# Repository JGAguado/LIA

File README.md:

[![License: CC BY-NC-SA 4.0][license-shield]](LICENSE)
[![Project Maintenance][maintenance-shield]][maintenance]
[![Powered by Meshtastic][meshtastic-shield]][meshtastic]
[![Documentation][docs-shield]][docs]

<p align="center">
    <picture>
      <source media="(prefers-color-scheme: dark)" srcset="https://raw.githubusercontent.com/JGAguado/LIA/main/website/src/assets/brand/Primary%20dark.png">
      <source media="(prefers-color-scheme: light)" srcset="https://raw.githubusercontent.com/JGAguado/LIA/main/website/src/assets/brand/Primary%20light.png">
      
    </picture>
</p>

**LIA** is an open-source, low-power pet and asset tracker built on top of [Meshtastic](https://meshtastic.org/) and LoRa mesh networking. It's designed to be a compact, long-range, subscription-free tracking device that keeps working off-grid — no cell coverage, no monthly fee, no cloud dependency.

📖 **[Read the full documentation](https://jgaguado.github.io/LIA/)**

<p align="center">
    
</p>

---

## Features

- Long-range LoRa communication over the open Meshtastic protocol
- GPS/GNSS location tracking, sent only as a direct message to a predefined target node — not visible to the wider public mesh
- A physical 3-position mode switch: continuous tracking (LED on, position every 30s), a low-power sleep cycle (wake roughly once a minute, get a fix, report it, sleep again), or fully OFF (cuts power to the MCU while still allowing the battery to charge)
- A text-command interface over the mesh: query position/battery on demand, toggle charge/motion notifications, override the status LED — see [Meshtastic Configuration](https://jgaguado.github.io/LIA/docs/firmware/meshtastic-configuration/)
- Deep-sleep, low-power firmware with real hardware wake sources (timer, mode-switch flip, charger plug-in)
- Subscription-free — no cloud backend required
- Fully open hardware: schematics, PCB layout, BOM, and enclosure CAD
- Compact, collar-mountable, waterproof-by-design enclosure — in three variants, see below

## Hardware Stack

**Core components**

- ESP32-S3-MINI-1 (MCU, Wi-Fi/BLE)
- SX1262 LoRa transceiver
- u-blox SAM-M10Q GNSS module
- MAX17048 battery fuel gauge

**Two hardware revisions, one firmware**

Both revisions carry the same reworked LSM6DSOXTR 6-axis IMU and run the identical `lia_v1` firmware — the only difference is the battery/enclosure:

- **V1.0** — 18650 Li-ion cell (3500 mAh) with magnetic pogo charging.
- **V1.1** — a 50×37×4 mm pouch cell (1000 mAh) instead, trading capacity for a much more compact enclosure.

**Antennas**

- Internal FPC LoRa antenna, or alternatively a standard omnidirectional linear 868/915 MHz antenna (e.g. [Seeed's LoRa Antenna Kit](https://www.seeedstudio.com/LoRa-Antenna-Kit-for-reTerminal-DM-p-5714.html))
- Ceramic GNSS patch antenna

See [Hardware documentation](https://jgaguado.github.io/LIA/docs/hardware/pcb/) for full details, and [Enclosure](https://jgaguado.github.io/LIA/docs/hardware/enclosure/) for the enclosure variants that pair with these boards.

## Software Stack

- [Meshtastic](https://meshtastic.org/) firmware
- [Astro](https://astro.build/) + [Starlight](https://starlight.astro.build/) + [Tailwind CSS](https://tailwindcss.com/) for this documentation site (fully static, no backend, no analytics, no cookies)

## Repository Structure

```
LIA/
├── website/       Astro + Starlight documentation & marketing site
├── firmware/       Meshtastic-based firmware (board variants, services, drivers, build tooling)
├── hardware/       KiCad project, PCB renders, schematics, BOM, production files
├── enclosure/       Enclosure CAD (gitignored native files), STEP/STL exports, renders — V1.0-Detachable/, V1.0-Fixed/, V1.1-Fixed/
├── mobile/         Companion mobile app (planned)
├── scripts/       Repo maintenance and tooling scripts
├── .github/       CI/CD workflows, issue & PR templates
├── LICENSE
├── CONTRIBUTING.md
├── CODE_OF_CONDUCT.md
└── README.md
```

## Quick Start

**Browse the docs:** https://jgaguado.github.io/LIA/

**Run the website locally:**

```sh
cd website
npm install
npm run dev
```

**Hardware:** open [`hardware/kicad/LIA.kicad_pro`](hardware/kicad/LIA.kicad_pro) in [KiCad](https://www.kicad.org/) 8+.

**Enclosure:** three versions — [`enclosure/V1.0-Detachable/`](enclosure/V1.0-Detachable), [`enclosure/V1.0-Fixed/`](enclosure/V1.0-Fixed), [`enclosure/V1.1-Fixed/`](enclosure/V1.1-Fixed) — each with its own `step/`/`stl/` exports and `drawings/`; no CAD license required to view or print them. See [Enclosure docs](https://jgaguado.github.io/LIA/docs/hardware/enclosure/) for what differs between them.

**Firmware:** see [`firmware/README.md`](firmware/README.md) and the [Getting Started guide](https://jgaguado.github.io/LIA/docs/getting-started/).

## Contributing

Contributions are welcome across hardware, firmware, mechanical design, and documentation. See [CONTRIBUTING.md](CONTRIBUTING.md) for how to get set up, and [CODE_OF_CONDUCT.md](CODE_OF_CONDUCT.md) for community guidelines.

## License

LIA is released under **[CC BY-NC-SA 4.0](LICENSE)** (Attribution-NonCommercial-ShareAlike). Personal, educational, and community use is welcome; commercial use requires permission from the maintainers. See the [License page](https://jgaguado.github.io/LIA/docs/license/) for details.

## Roadmap
- [x] Draft project requirements and design goals
- [x] Complete first hardware revision (V1.0) and a second, more compact revision (V1.1)
- [x] Complete first enclosure revisions — V1.0-Detachable, V1.0-Fixed, and V1.1-Fixed
- [x] Manufacture and assemble first batch of boards
- [x] Smoke-test and validate hardware (radio, GPS, charging, battery gauge, IMU)
- [x] Release first firmware — see [Development History](https://jgaguado.github.io/LIA/docs/development-history/) for the phase-by-phase log
- [x] Release initial documentation
- [x] Field trial: real-world tracking validation over an extended period
- [x] Measured (not estimated) battery runtime numbers

## Disclaimer

LIA is an experimental open-source project and should not be considered a guaranteed real-time safety tracking solution.

[license-shield]: https://img.shields.io/badge/License-CC%20BY--NC--SA%204.0-lightgrey.svg?style=for-the-badge
[maintenance-shield]: https://img.shields.io/badge/maintainer-J.%20G.%20Aguado-2e48a7.svg?style=for-the-badge
[maintenance]: https://github.com/JGAguado
[meshtastic-shield]: https://img.shields.io/badge/Powered%20by-Meshtastic-67EA94.svg?style=for-the-badge
[meshtastic]: https://meshtastic.org/
[docs-shield]: https://img.shields.io/badge/Documentation-online-2e48a7.svg?style=for-the-badge
[docs]: https://jgaguado.github.io/LIA/

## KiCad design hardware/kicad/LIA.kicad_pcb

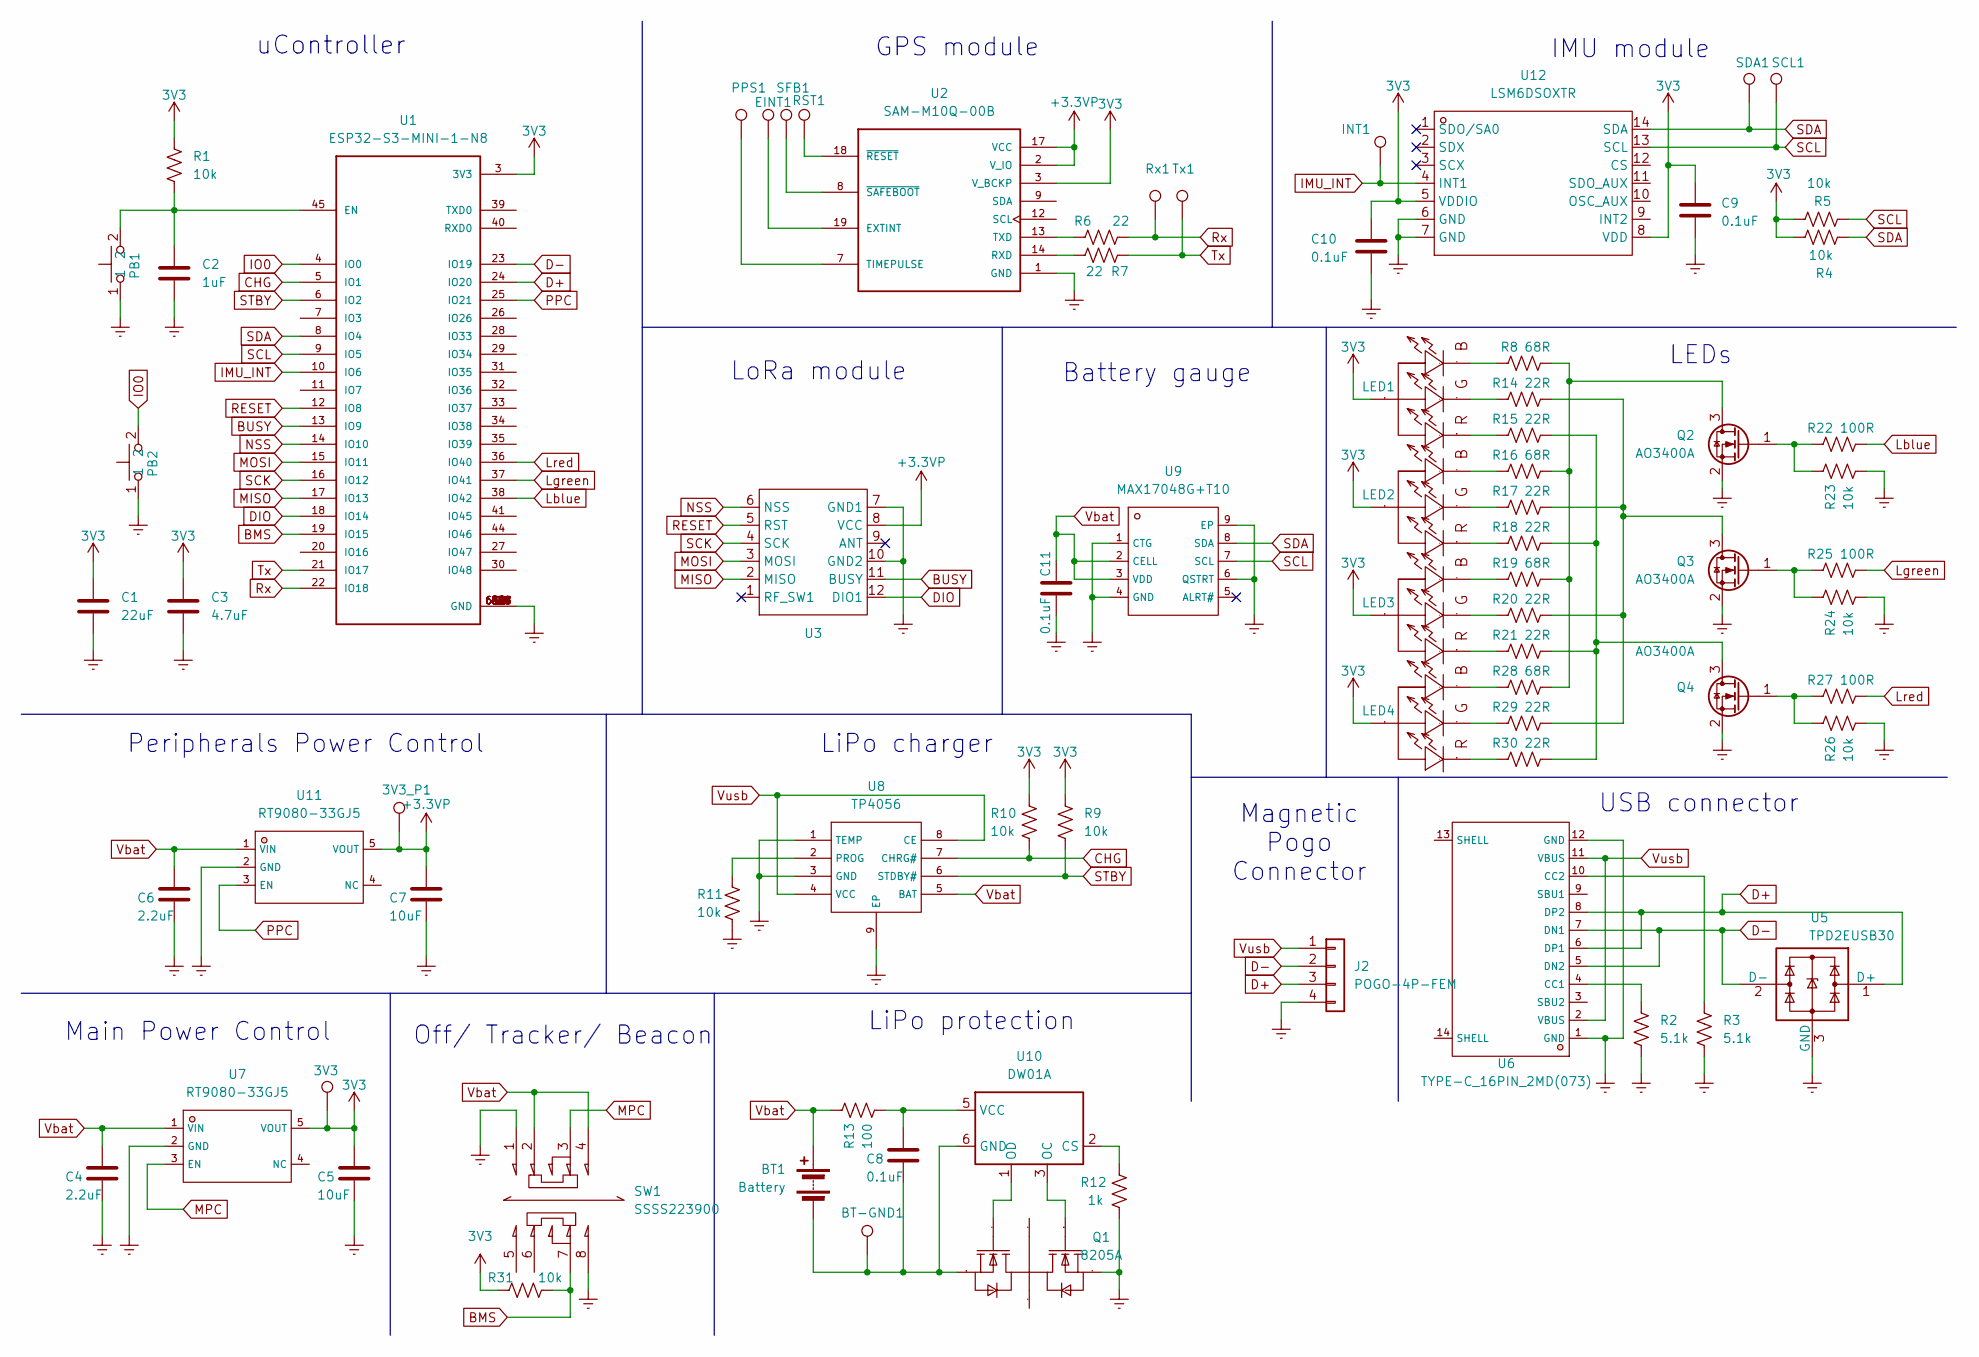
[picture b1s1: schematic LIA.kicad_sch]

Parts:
3V3, 3V3_P1: TestPoint; TestPoint_Pad_D1.0mm
BT1: Battery; BatteryClip_Keystone_54_D16-19mm
BT-GND1: TestPoint; TestPoint_Pad_D1.0mm
C1: 22uF; C_0805_2012Metric
C2: 1uF; C_0201_0603Metric
C3: 4.7uF; C_0201_0603Metric
C4, C6: 2.2uF; C_0201_0603Metric
C5, C7: 10uF; C_0603_1608Metric
C8, C9, C10, C11: 0.1uF; C_0201_0603Metric
EINT1: TestPoint; TestPoint_Pad_D1.0mm
INT1: TestPoint; TestPoint_Pad_D1.0mm
J2: POGO-4P-FEM; POGO-MAG-4P-FEM
LED1, LED2, LED3, LED4: MHS110CRGBCT; LED-SMD_4P-L3.2-W1.1_TJ-S3210SW5TCGLC2R2G-A5; Manufacturer Part MHS110CRGBCT; LCSC Part Name RGB三色 侧贴
PB1: TS-1088-AR02016; SW-SMD_L3.9-W3.0-P4.45; LCSC C318884
PB2: TS-1088-AR02016; SW-SMD_L3.9-W3.0-P4.45; LCSC C115357
PPS1: TestPoint; TestPoint_Pad_D1.0mm
Q1: 8205A; SOT-23-6_L2.9-W1.6-P0.95-LS2.8-BL; Manufacturer Part 8205A SOT23-6-VB; LCSC C351449
Q2, Q3, Q4: AO3400A; SOT-23
R1, R4, R5, R9, R10, R11, R23, R24, R26, R31: 10k; R_0201_0603Metric
R2, R3: 5.1k; R_0201_0603Metric
R6, R7: 22; R_0201_0603Metric
R8, R16, R19, R28: 68R; R_0201_0603Metric
R12: 1k; R_0201_0603Metric
R13: 100; R_0201_0603Metric
R14, R15, R17, R18, R20, R21, R29, R30: 22R; R_0201_0603Metric
R22, R25, R27: 100R; R_0201_0603Metric
RST1: TestPoint; TestPoint_Pad_D1.0mm
Rx1: TestPoint; TestPoint_Pad_D1.0mm
SCL1: TestPoint; TestPoint_Pad_D1.0mm
SDA1: TestPoint; TestPoint_Pad_D1.0mm
SFB1: TestPoint; TestPoint_Pad_D1.0mm
SW1: SSSS223900; SW-TH_SSSS223900; Manufacturer Part SSSS223900; LCSC Part Name SSSS223900
Tx1: TestPoint; TestPoint_Pad_D1.0mm
U1: ESP32-S3-MINI-1-N8; XCVR_ESP32-S3-MINI-1-N8; PARTREV v0.6; LCSC C2913206
U2: SAM-M10Q-00B; XCVR_SAM-M10Q-00B; PARTREV R03
U3: Wio-SX1262; MODULE12P-1.27-11X11.6MM
U5: TPD2EUSB30; Texas_DRT-3
U6: TYPE-C_16PIN_2MD(073); USB-C-SMD_TYPE-C-6PIN-2MD-073; LCSC C2765186
U7, U11: RT9080-33GJ5; TSOT-23-5_L2.9-W1.6-P0.95-LS2.8-BL; LCSC C841192
U8: TP4056; ESOP-8_L4.9-W3.9-P1.27-LS6.0-BL-EP; LCSC C16581
U9: MAX17048G+T10; DFN-8_L2.0-W2.0-P0.50-BL-EP; LCSC C2682616
U10: DW01A; SOT-23-6
U12: LSM6DSOXTR; LGA-14L_L3.0-W2.5-P0.50-TL; Manufacturer Part LSM6DSOXTR; LCSC C481766

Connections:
3V3: 3V3.1, C1.2, C3.2, C5.2, C9.2, C10.2, LED1.1 (+), LED2.1 (+), LED3.1 (+), LED4.1 (+), R1.1, R4.1, R5.1, R9.1, R10.1, R31.1, U1.3 (3V3), U2.3 (V_BCKP), U7.5 (VOUT), U12.5 (VDDIO), U12.8 (VDD)
+3.3VP: 3V3_P1.1, C7.2, U2.2 (V_IO), U2.17 (VCC), U3.8 (VCC), U11.5 (VOUT)
BMS: R31.2, SW1.7, U1.19 (IO15)
BUSY: U1.13 (IO9), U3.11 (BUSY)
CHG: R10.2, U1.5 (IO1), U8.7 (CHRG#)
D+: J2.3, U1.24 (IO20), U5.1 (D+), U6.6 (DP1), U6.8 (DP2)
D-: J2.2, U1.23 (IO19), U5.2 (D-), U6.5 (DN2), U6.7 (DN1)
DIO: U1.18 (IO14), U3.12 (DIO1)
GND: C1.1, C2.1, C3.1, C4.1, C5.1, C6.1, C7.1, C9.1, C10.1, C11.1, J2.4, PB1.1, PB2.1, Q1.3 (S), Q2.2 (S), Q3.2 (S), Q4.2 (S), R2.2, R3.2, R11.2, R12.2, R23.2, R24.2, R26.2, SW1.1, SW1.8, U1.1 (GND), U1.2 (GND), U1.42 (GND), U1.43 (GND), U1.46 (GND), U1.47 (GND), U1.48 (GND), U1.49 (GND), U1.50 (GND), U1.51 (GND), U1.52 (GND), U1.53 (GND), U1.54 (GND), U1.55 (GND), U1.56 (GND), U1.57 (GND), U1.58 (GND), U1.59 (GND), U1.60 (GND), U1.61 (GND), U1.61_1 (GND), U1.61_2 (GND), U1.61_3 (GND), U1.61_4 (GND), U1.61_5 (GND), U1.61_6 (GND), U1.61_7 (GND), U1.61_8 (GND), U1.62 (GND), U1.63 (GND), U1.64 (GND), U1.65 (GND), U2.1 (GND), U2.4 (GND), U2.5 (GND), U2.6 (GND), U2.10 (GND), U2.11 (GND), U2.15 (GND), U2.16 (GND), U2.20 (GND), U3.7 (GND1), U3.10 (GND2), U5.3 (GND), U6.1 (GND), U6.12 (GND), U7.2 (GND), U8.1 (TEMP), U8.3 (GND), U8.9 (EP), U9.1 (CTG), U9.4 (GND), U9.6 (QSTRT), U9.9 (EP), U11.2 (GND), U12.6 (GND), U12.7 (GND)
IMU_INT: INT1.1, U1.10 (IO6), U12.4 (INT1)
IO0: PB2.2, U1.4 (IO0)
Lblue: R22.2, U1.38 (IO42)
Lgreen: R25.2, U1.37 (IO41)
Lred: R27.2, U1.36 (IO40)
MISO: U1.17 (IO13), U3.2 (MISO)
MOSI: U1.15 (IO11), U3.3 (MOSI)
MPC: SW1.3, U7.3 (EN)
NSS: U1.14 (IO10), U3.6 (NSS)
unnamed: BT1.2 (-), BT-GND1.1, C8.1, Q1.1 (S), U10.6 (GND)
unnamed: LED1.2 (-), R8.1
unnamed: LED1.3 (-), R14.1
unnamed: LED1.4 (-), R15.1
unnamed: LED2.2 (-), R16.1
unnamed: LED2.3 (-), R17.1
unnamed: LED2.4 (-), R18.1
unnamed: LED3.2 (-), R19.1
unnamed: LED3.3 (-), R20.1
unnamed: LED3.4 (-), R21.1
unnamed: LED4.2 (-), R28.1
unnamed: LED4.3 (-), R29.1
unnamed: LED4.4 (-), R30.1
unnamed: Q2.3 (D), R8.2, R16.2, R19.2, R28.2
unnamed: Q2.1 (G), R22.1, R23.1
unnamed: Q3.3 (D), R14.2, R17.2, R20.2, R29.2
unnamed: Q3.1 (G), R24.1, R25.1
unnamed: Q4.3 (D), R15.2, R18.2, R21.2, R30.2
unnamed: Q4.1 (G), R26.1, R27.1
unnamed: C2.2, PB1.2, R1.2, U1.45 (EN)
unnamed: EINT1.1, U2.19 (EXTINT)
unnamed: R7.2, U2.14 (RXD)
unnamed: PPS1.1, U2.7 (TIMEPULSE)
unnamed: R6.1, U2.13 (TXD)
unnamed: RST1.1, U2.18 (~RESET)
unnamed: SFB1.1, U2.8 (~SAFEBOOT)
unnamed: R2.1, U6.4 (CC1)
unnamed: R3.1, U6.10 (CC2)
unnamed: R11.1, U8.2 (PROG)
unnamed: R12.1, U10.2 (CS)
unnamed: Q1.4 (G), U10.3 (OC)
unnamed: Q1.6 (G), U10.1 (OD)
unnamed: C8.2, R13.2, U10.5 (VCC)
PPC: U1.25 (IO21), U11.3 (EN)
RESET: U1.12 (IO8), U3.5 (RST)
Rx: R6.2, Rx1.1, U1.22 (IO18)
SCK: U1.16 (IO12), U3.4 (SCK)
STBY: R9.2, U1.6 (IO2), U8.6 (STDBY#)
Tx: R7.1, Tx1.1, U1.21 (IO17)
Vbat: BT1.1 (+), C4.2, C6.2, C11.2, R13.1, SW1.2, SW1.4, U7.1 (VIN), U8.5 (BAT), U9.2 (CELL), U9.3 (VDD), U11.1 (VIN)
Vusb: J2.1, U6.2 (VBUS), U6.11 (VBUS), U8.4 (VCC), U8.8 (CE)

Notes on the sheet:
Battery gauge
Off/ Tracker/ Beacon
LoRa module
Main Power Control
LiPo protection
IMU module
uController
Magnetic Pogo Connector
USB connector
LiPo charger
GPS module
Peripherals Power Control
LEDs

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
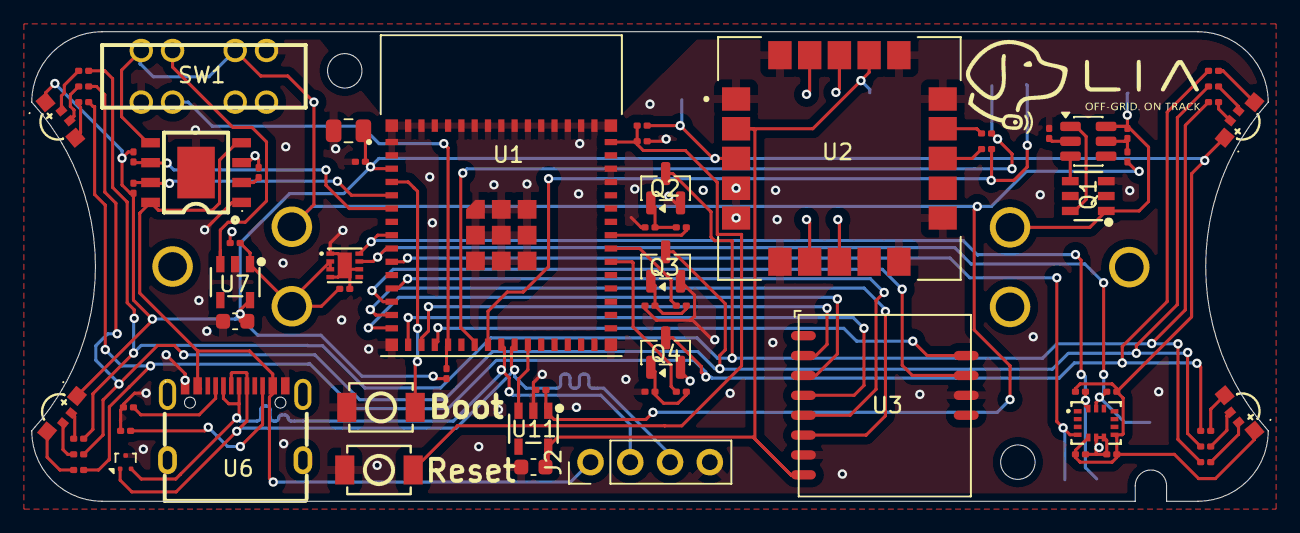
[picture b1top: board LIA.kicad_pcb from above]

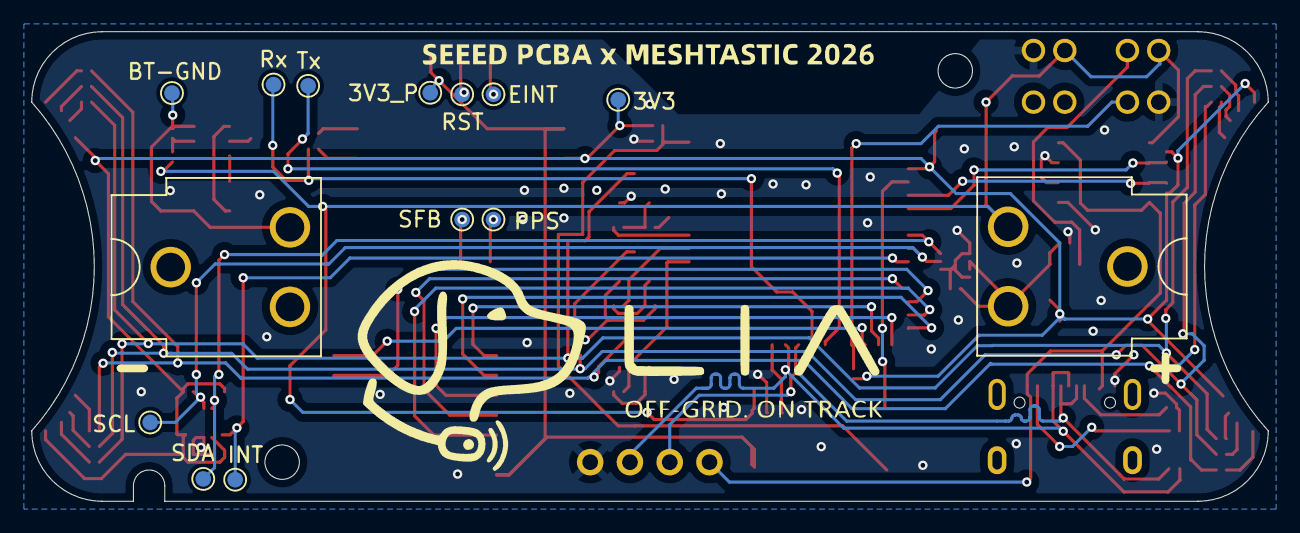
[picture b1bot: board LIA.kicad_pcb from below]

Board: 2 copper layers, 79.0 x 30.0 mm, 78 parts (13 on the bottom side), 61 nets.

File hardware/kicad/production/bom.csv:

Designator,Footprint,Quantity,Value,LCSC Part #
"3V3, 3V3_P1, BT-GND1, EINT1, INT1, PPS1, RST1, RX1, SCL1, SDA1, SFB1, TX1",TestPoint_Pad_D1.0mm,12,TestPoint,
BT1,BatteryClip_Keystone_54_D16-19mm,1,Battery,
C1,0805,1,22uF,
"C10, C11, C8, C9",0201,4,0.1uF,
C2,0201,1,1uF,
C3,0201,1,4.7uF,
"C4, C6",0201,2,2.2uF,
"C5, C7",0603,2,10uF,
J2,POGO-MAG-4P-FEM,1,POGO-4P-FEM,
"LED1, LED2, LED3, LED4",LED-SMD_4P-L3.2-W1.1_TJ-S3210SW5TCGLC2R2G-A5,4,MHS110CRGBCT,
PB1,SW-SMD_L3.9-W3.0-P4.45,1,TS-1088-AR02016,C318884
PB2,SW-SMD_L3.9-W3.0-P4.45,1,TS-1088-AR02016,C115357
Q1,SOT-23-6_L2.9-W1.6-P0.95-LS2.8-BL,1,8205A,C351449
"Q2, Q3, Q4",SOT-23,3,AO3400A,
"R1, R10, R11, R23, R24, R26, R31, R4, R5, R9",0201,10,10k,
R12,0201,1,1k,
R13,0201,1,100,
"R14, R15, R17, R18, R20, R21, R29, R30",0201,8,22R,
"R16, R19, R28, R8",0201,4,68R,
"R2, R3",0201,2,5.1k,
"R22, R25, R27",0201,3,100R,
"R6, R7",0201,2,22,
SW1,SW-TH_SSSS223900,1,SSSS223900,
U1,XCVR_ESP32-S3-MINI-1-N8,1,ESP32-S3-MINI-1-N8,C2913206
U10,SOT-23-6,1,DW01A,
"U11, U7",TSOT-23-5_L2.9-W1.6-P0.95-LS2.8-BL,2,RT9080-33GJ5,C841192
U12,LGA-14L_L3.0-W2.5-P0.50-TL,1,LSM6DSOXTR,C481766
U2,XCVR_SAM-M10Q-00B,1,SAM-M10Q-00B,
U3,MODULE12P-1.27-11X11.6MM,1,Wio-SX1262,
U5,Texas_DRT-3,1,TPD2EUSB30,
U6,USB-C-SMD_TYPE-C-6PIN-2MD-073,1,TYPE-C_16PIN_2MD(073),C2765186
U8,ESOP-8_L4.9-W3.9-P1.27-LS6.0-BL-EP,1,TP4056,C16581
U9,DFN-8_L2.0-W2.0-P0.50-BL-EP,1,MAX17048G+T10,C2682616

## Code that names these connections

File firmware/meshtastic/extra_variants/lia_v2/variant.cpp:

#include "configuration.h"

#ifdef _VARIANT_LIA_V2

#include "esp_sleep.h"
#include "lia/LiaBoard.h"

// Identical to lia_v1's earlyInitVariant() -- see that file for why PPC is
// enabled here and why there's no logging. This revision's I2C bus (battery
// gauge) isn't touched here: Meshtastic's stock main.cpp calls
// Wire.begin(I2C_SDA, I2C_SCL) and scans it independently of anything in
// this file, since variant.h defines those macros.
void earlyInitVariant()
{
    LiaBoard::instance().begin();
    LiaBoard::instance().enablePeripherals();
}

#include "lia/services/ChargeStatusService.h"
#include "lia/services/TrackerService.h"

void lateInitVariant()
{
    LOG_INFO("LiaBoard: peripherals=%d (PPC=GPIO%d)", LiaBoard::instance().peripheralsEnabled(), LIA_PIN_PPC);

    // See lia_v1/variant.cpp's lateInitVariant() for why this must run here
    // and not from begin()/earlyInitVariant() -- unchanged on this revision.
    LiaBoard::instance().armDeepSleepHook();

    new TrackerService();
    new ChargeStatusService();
}

// See lia_v1/variant.cpp's variant_shutdown() for the full rationale --
// unchanged on this revision (BMS/CHG pins are the same).
void variant_shutdown()
{
    esp_sleep_enable_ext0_wakeup((gpio_num_t)LIA_PIN_CHG, LOW);
    esp_sleep_enable_ext1_wakeup(1ULL << LIA_PIN_BMS, ESP_EXT1_WAKEUP_ANY_HIGH);
}

#endif // _VARIANT_LIA_V2
